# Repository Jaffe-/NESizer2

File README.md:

## NESizer2: 2A03 Synthesizer Project

The main idea of this project is to use an isolated NES 2A03 CPU/APU IC as a stand-alone synthesizer, controlled by an Atmel Atmega microcontroller. (The project is named NESizer2 after a failed attempt to create a NES synthesizer using only the 2A03 alone, with its own ROM, RAM and I/O logic.)

The 2A03 IC consists of a 6502 CPU core (with some minor changes), a DMA controller and the Audio Processing Unit. The APU is controlled via 22 registers, which are connected internally to the 6502 only; there are no external input pins facilitating communication with the APU directly. This means that in order to control the APU, the 6502 must act as a proxy: The microcontroller must send the 6502 instructions to take a value and put it in a desired APU register.

This project is inspired by a similar approach taken here: http://www.soniktech.com/tsundere/, but the idea here is to have the microcontroller communicate more directly with the 2A03, with a minimum of circuitry to do so.

Check out the most recent demo [here](https://www.youtube.com/watch?v=pXKrs0bFvvk)!

See the documentation for a description of how the NESizer works:

- [Hardware documentation](docs/hardware.md)
- [Software documentation](docs/software.md)

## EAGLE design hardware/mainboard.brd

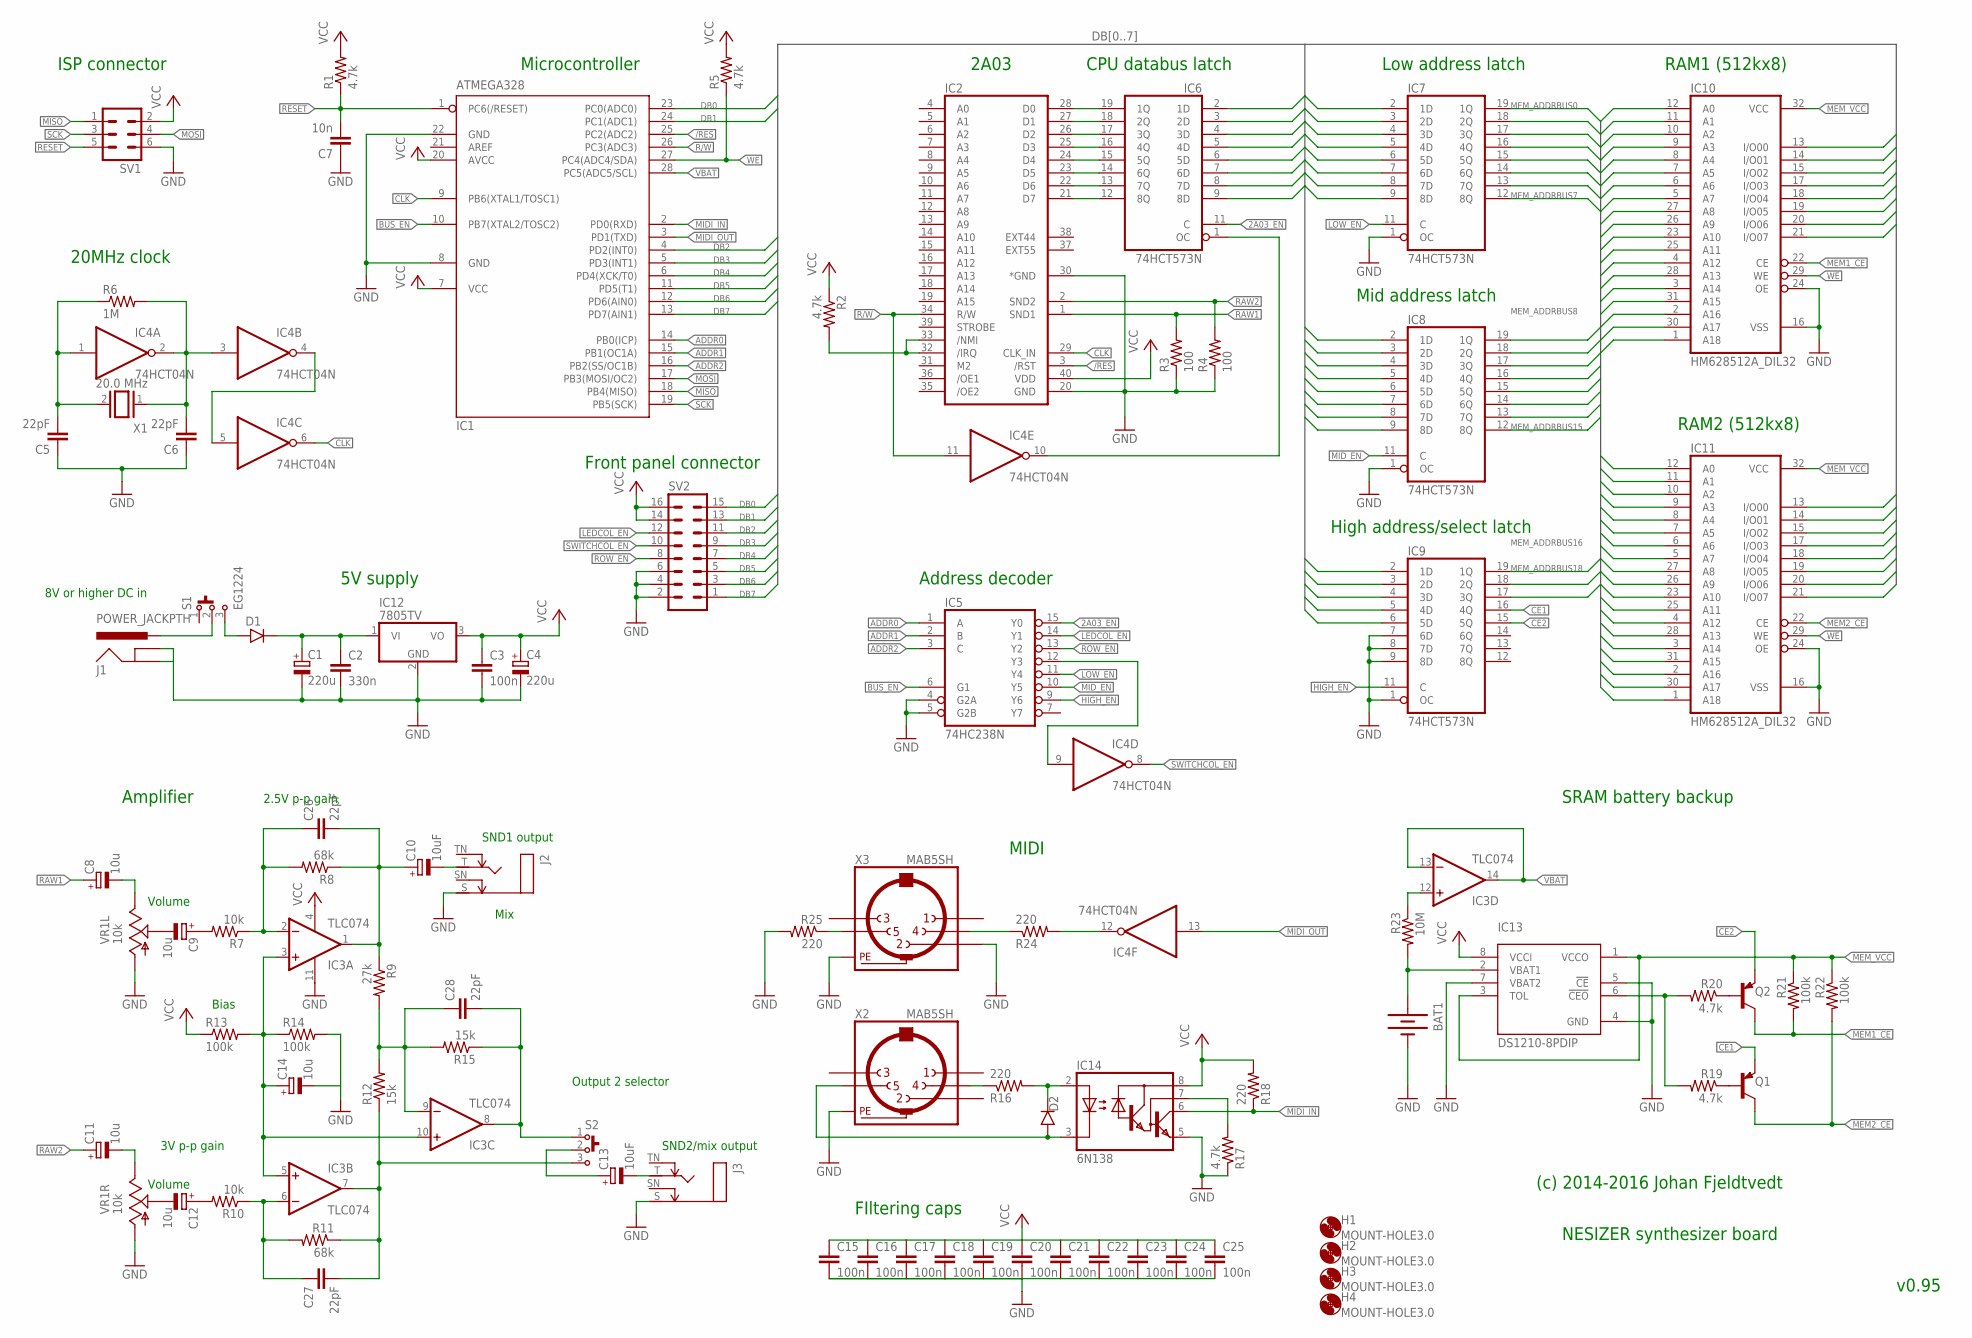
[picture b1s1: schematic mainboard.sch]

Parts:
BAT1: BATTERY20PTH; BATTCOM_20MM_PTH
C1, C4: 220u; E5-10,5
C2: 330n; C025-025X050
C3, C15, C16, C17, C18, C19, C20, C21, C22, C23, C24, C25: 100n; C025-025X050
C5, C6, C26, C27, C28: 22pF; C2.5-2
C7: 10n; C2.5-2
C8, C9, C11, C12, C14: 10u; E2-5
C10, C13: 10uF; E2-5
D1: 1N400X.3; DO41-3
D2: 1N914.3; DO35-3
H1, H2, H3, H4: MOUNT-HOLE3.0; 3,0
IC1: ATMEGA328; DIL28-3
IC2: 2A03; DIL40
IC3: TLC074; DIL14
IC4: 74HCT04N; DIL14
IC5: 74HC238N; DIL16
IC6, IC7, IC8, IC9: 74HCT573N; DIL20
IC10, IC11: HM628512A_DIL32; DIL32
IC12: 7805TV; TO220V
IC13: DS1210-8PDIP; DIL08
IC14: 6N138; DIL08
J1: POWER_JACKPTH; POWER_JACK_PTH
J2, J3: MONOSW; NMJ4HCD2
Q1, Q2: BC557; TO92
R1, R2, R5, R17, R19, R20: 4.7k; 0207/7
R3, R4: 100; 0207/7
R6: 1M; 0207/7
R7, R10: 10k; 0207/7
R8, R11: 68k; 0207/7
R9: 27k; 0207/7
R12, R15: 15k; 0207/7
R13, R14, R21, R22: 100k; 0207/7
R16, R18, R24, R25: 220; 0207/7
R23: 10M; 0207/7
S1, S2: EG1224
SV1: MA03-2
SV2: MA08-2
VR1: 10k; ALPS_RK0971221Z0X
X1: 20.0 MHz; QS
X2, X3: MAB5SH

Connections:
2A03_EN: IC5.15 (Y0), IC6.11 (C)
/RES: IC1.25 (PC2(ADC2)), IC2.3 (/RST)
ADDR0: IC1.14 (PB0(ICP)), IC5.1 (A)
ADDR1: IC1.15 (PB1(OC1A)), IC5.2 (B)
ADDR2: IC1.16 (PB2(SS/OC1B)), IC5.3 (C)
BUS_EN: IC1.10 (PB7(XTAL2/TOSC2)), IC5.6 (G1)
C6: C8.-, VR1.I1 (3)
CE1: IC9.16 (4Q), Q1.1 (E)
CE2: IC9.15 (5Q), Q2.1 (E)
CLK: IC1.9 (PB6(XTAL1/TOSC1)), IC2.29 (CLK_IN), IC4.6 (O)
DB0: IC1.23 (PC0(ADC0)), IC6.2 (1D), IC7.2 (1D), IC8.2 (1D), IC9.2 (1D), IC10.13 (I/O00), IC11.13 (I/O00), SV2.15
DB1: IC1.24 (PC1(ADC1)), IC6.3 (2D), IC7.3 (2D), IC8.3 (2D), IC9.3 (2D), IC10.14 (I/O01), IC11.14 (I/O01), SV2.13
DB2: IC1.4 (PD2(INT0)), IC6.4 (3D), IC7.4 (3D), IC8.4 (3D), IC9.4 (3D), IC10.15 (I/O02), IC11.15 (I/O02), SV2.11
DB3: IC1.5 (PD3(INT1)), IC6.5 (4D), IC7.5 (4D), IC8.5 (4D), IC9.5 (4D), IC10.17 (I/O03), IC11.17 (I/O03), SV2.9
DB4: IC1.6 (PD4(XCK/T0)), IC6.6 (5D), IC7.6 (5D), IC8.6 (5D), IC9.6 (5D), IC10.18 (I/O04), IC11.18 (I/O04), SV2.7
DB5: IC1.11 (PD5(T1)), IC6.7 (6D), IC7.7 (6D), IC8.7 (6D), IC10.19 (I/O05), IC11.19 (I/O05), SV2.5
DB6: IC1.12 (PD6(AIN0)), IC6.8 (7D), IC7.8 (7D), IC8.8 (7D), IC10.20 (I/O06), IC11.20 (I/O06), SV2.3
DB7: IC1.13 (PD7(AIN1)), IC6.9 (8D), IC7.9 (8D), IC8.9 (8D), IC10.21 (I/O07), IC11.21 (I/O07), SV2.1
GND: BAT1.2 (-), C1.-, C2.2, C3.2, C4.-, C5.1, C6.1, C7.1, C14.-, C15.2, C16.2, C17.2, C18.2, C19.2, C20.2, C21.2, C22.2, C23.2, C24.2, C25.2, IC1.8 (GND), IC1.22 (GND), IC2.20 (GND), IC2.30 (*GND), IC3.11 (V-), IC4.7 (GND), IC5.4 (G2A), IC5.5 (G2B), IC5.8 (GND), IC6.10 (GND), IC7.1 (OC), IC7.10 (GND), IC8.1 (OC), IC8.10 (GND), IC9.1 (OC), IC9.7 (6D), IC9.8 (7D), IC9.9 (8D), IC9.10 (GND), IC10.16 (VSS), IC10.24 (OE), IC11.16 (VSS), IC11.24 (OE), IC12.2 (GND), IC13.4 (GND), IC13.5 (!CE), IC13.7 (VBAT2), IC14.5 (GND), J1.GND, J1.GNDBREAK, J2.S, J3.S, R3.1, R4.1, R14.2, R17.1, R25.2, SV1.6, SV2.2, SV2.4, SV2.6, VR1.G1 (1), VR1.G2 (1), X2.PE, X2.PE@ (PE), X3.2, X3.PE, X3.PE@ (PE)
HIGH_EN: IC5.9 (Y6), IC9.11 (C)
LEDCOL_EN: IC5.14 (Y1), SV2.12
LOW_EN: IC5.11 (Y4), IC7.11 (C)
MEM1_CE: IC10.22 (CE), Q2.3 (C), R21.2
MEM2_CE: IC11.22 (CE), Q1.3 (C), R22.2
MEM_ADDRBUS0: IC7.19 (1Q), IC10.12 (A0), IC11.12 (A0)
MEM_ADDRBUS1: IC7.18 (2Q), IC10.11 (A1), IC11.11 (A1)
MEM_ADDRBUS2: IC7.17 (3Q), IC10.10 (A2), IC11.10 (A2)
MEM_ADDRBUS3: IC7.16 (4Q), IC10.9 (A3), IC11.9 (A3)
MEM_ADDRBUS4: IC7.15 (5Q), IC10.8 (A4), IC11.8 (A4)
MEM_ADDRBUS5: IC7.14 (6Q), IC10.7 (A5), IC11.7 (A5)
MEM_ADDRBUS6: IC7.13 (7Q), IC10.6 (A6), IC11.6 (A6)
MEM_ADDRBUS7: IC7.12 (8Q), IC10.5 (A7), IC11.5 (A7)
MEM_ADDRBUS8: IC8.19 (1Q), IC10.27 (A8), IC11.27 (A8)
MEM_ADDRBUS9: IC8.18 (2Q), IC10.26 (A9), IC11.26 (A9)
MEM_ADDRBUS10: IC8.17 (3Q), IC10.23 (A10), IC11.23 (A10)
MEM_ADDRBUS11: IC8.16 (4Q), IC10.25 (A11), IC11.25 (A11)
MEM_ADDRBUS12: IC8.15 (5Q), IC10.4 (A12), IC11.4 (A12)
MEM_ADDRBUS13: IC8.14 (6Q), IC10.28 (A13), IC11.28 (A13)
MEM_ADDRBUS14: IC8.13 (7Q), IC10.3 (A14), IC11.3 (A14)
MEM_ADDRBUS15: IC8.12 (8Q), IC10.31 (A15), IC11.31 (A15)
MEM_ADDRBUS16: IC9.19 (1Q), IC10.2 (A16), IC11.2 (A16)
MEM_ADDRBUS17: IC9.18 (2Q), IC10.30 (A17), IC11.30 (A17)
MEM_ADDRBUS18: IC9.17 (3Q), IC10.1 (A18), IC11.1 (A18)
MEM_VCC: IC10.32 (VCC), IC11.32 (VCC), IC13.1 (VCCO), IC13.3 (TOL), R21.1, R22.1
MIDI_IN: IC1.2 (PD0(RXD)), IC14.6 (VO), R18.1
MIDI_OUT: IC1.3 (PD1(TXD)), IC4.13 (I)
MIDI_PIN_4: R16.1, X2.4
MIDI_PIN_5: D2.A, IC14.3 (C), X2.5
MID_EN: IC5.10 (Y5), IC8.11 (C)
MISO: IC1.18 (PB4(MISO)), SV1.1
MOSI: IC1.17 (PB3(MOSI/OC2)), SV1.4
unnamed: C5.2, IC4.1 (I), R6.1, X1.2
unnamed: C6.2, IC4.2 (O), IC4.3 (I), R6.2, X1.1
unnamed: IC2.21 (D7), IC6.12 (8Q)
unnamed: IC2.22 (D6), IC6.13 (7Q)
unnamed: IC2.23 (D5), IC6.14 (6Q)
unnamed: IC2.24 (D4), IC6.15 (5Q)
unnamed: IC2.25 (D3), IC6.16 (4Q)
unnamed: IC2.26 (D2), IC6.17 (3Q)
unnamed: IC2.27 (D1), IC6.18 (2Q)
unnamed: IC2.28 (D0), IC6.19 (1Q)
unnamed: IC4.4 (O), IC4.5 (I)
unnamed: IC4.9 (I), IC5.12 (Y3)
unnamed: C13.+, S2.2
unnamed: C28.1, IC3.9 (-IN), R9.2, R12.2, R15.2
unnamed: C9.+, R7.2
unnamed: IC2.32 (/IRQ), IC2.33 (/NMI), R2.2
unnamed: C11.-, VR1.I2 (3)
unnamed: C26.1, IC3.2 (-IN), R7.1, R8.2
unnamed: IC3.12 (+IN), R23.1
unnamed: IC14.7 (VB), R17.2
unnamed: C12.+, R10.2
unnamed: C10.-, J2.T
unnamed: C13.-, J3.T
unnamed: C27.1, IC3.6 (-IN), R10.1, R11.2
unnamed: C10.+, C26.2, IC3.1 (OUT), R8.1, R9.1
unnamed: C28.2, IC3.8 (OUT), R15.1, S2.1
unnamed: D1.A, S1.3
unnamed: C14.+, IC3.3 (+IN), IC3.5 (+IN), IC3.10 (+IN), R13.2, R14.1
unnamed: IC4.10 (O), IC6.1 (OC)
unnamed: C9.-, VR1.O1 (2)
unnamed: J1.PWR, S1.2
unnamed: C12.-, VR1.O2 (2)
unnamed: IC13.6 (!CEO), R19.2, R20.2
unnamed: D2.C, IC14.2 (A), R16.2
unnamed: C1.+, C2.1, D1.C, IC12.1 (VI)
unnamed: C27.2, IC3.7 (OUT), R11.1, R12.1, S2.3
unnamed: Q1.2 (B), R19.1
unnamed: Q2.2 (B), R20.1
unnamed: BAT1.1 (+), IC13.2 (VBAT1), R23.2
unnamed: IC4.12 (O), R24.2
unnamed: R24.1, X3.4
unnamed: R25.1, X3.5
R/W: IC1.26 (PC3(ADC3)), IC2.34 (R/W), IC4.11 (I)
RAW1: C8.+, IC2.1 (SND1), R3.2
RAW2: C11.+, IC2.2 (SND2), R4.2
RESET: C7.2, IC1.1 (PC6(/RESET)), R1.1, SV1.5
ROW_EN: IC5.13 (Y2), SV2.8
S1: VR1.S1
S2: VR1.S2
SCK: IC1.19 (PB5(SCK)), SV1.3
SWITCHCOL_EN: IC4.8 (O), SV2.10
VBAT: IC1.28 (PC5(ADC5/SCL)), IC3.13 (-IN), IC3.14 (OUT)
VCC: C3.1, C4.+, C15.1, C16.1, C17.1, C18.1, C19.1, C20.1, C21.1, C22.1, C23.1, C24.1, C25.1, IC1.7 (VCC), IC1.20 (AVCC), IC2.40 (VDD), IC3.4 (V+), IC4.14 (VCC), IC5.16 (VCC), IC6.20 (VCC), IC7.20 (VCC), IC8.20 (VCC), IC9.20 (VCC), IC12.3 (VO), IC13.8 (VCCI), IC14.8 (VCC), R1.2, R2.1, R5.2, R13.1, R18.2, SV1.2, SV2.14, SV2.16
WE: IC1.27 (PC4(ADC4/SDA)), IC10.29 (WE), IC11.29 (WE), R5.1

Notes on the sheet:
Microcontroller
2A03
ISP connector
20MHz clock
Amplifier
Address decoder
CPU databus latch
RAM1 (512kx8)
RAM2 (512kx8)
Low address latch
Mid address latch
High address/select latch
Front panel connector
SRAM battery backup
MIDI
5V supply
FIltering caps
SND2/mix output
SND1 output
8V or higher DC in
Volume
Output 2 selector
2.5V p-p gain
3V p-p gain
Mix
v0.95
(c) 2014-2016 Johan Fjeldtvedt
NESIZER synthesizer board
Bias

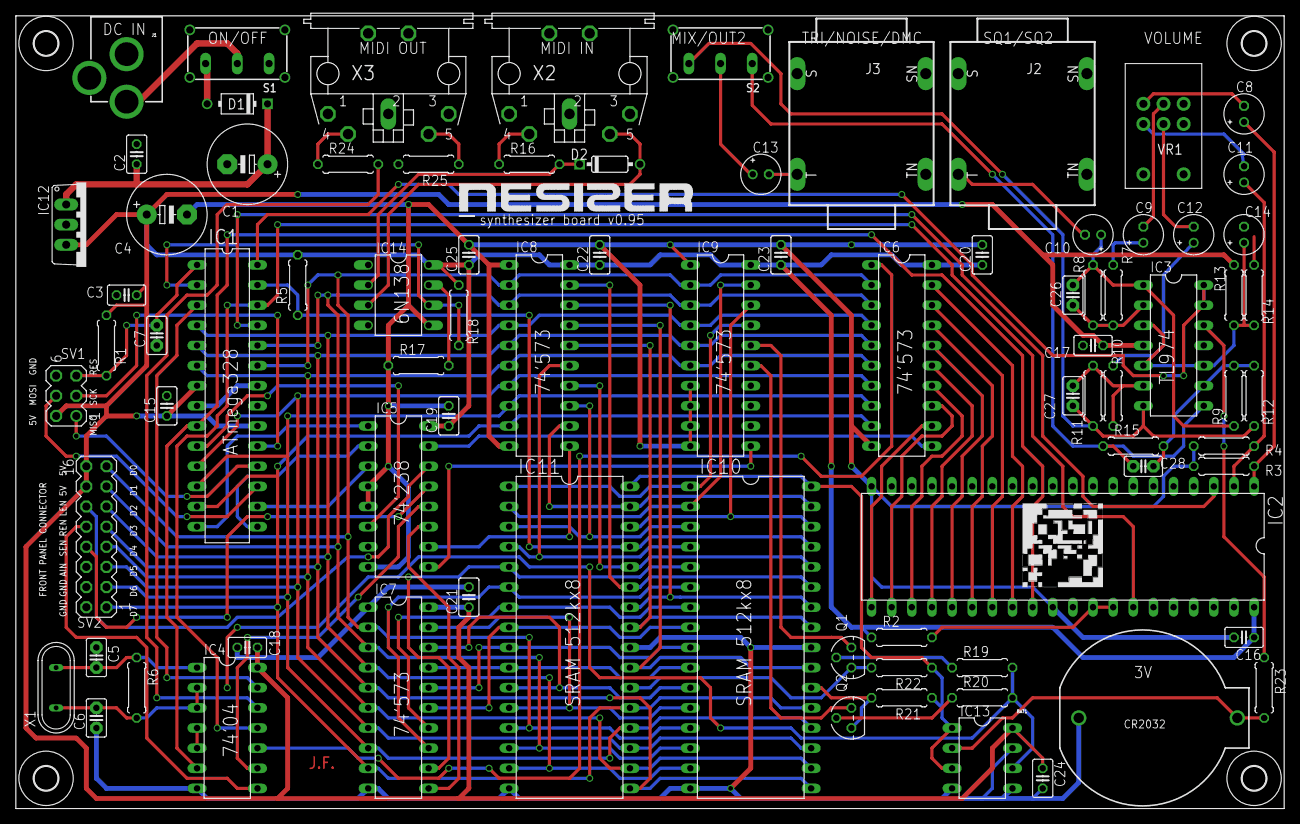
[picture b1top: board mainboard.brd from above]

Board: 2 copper layers, 160.0 x 100.0 mm, 89 parts (0 on the bottom side), 103 nets.

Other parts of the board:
U$1: NESIZER_LOGO
U$2: MARIO

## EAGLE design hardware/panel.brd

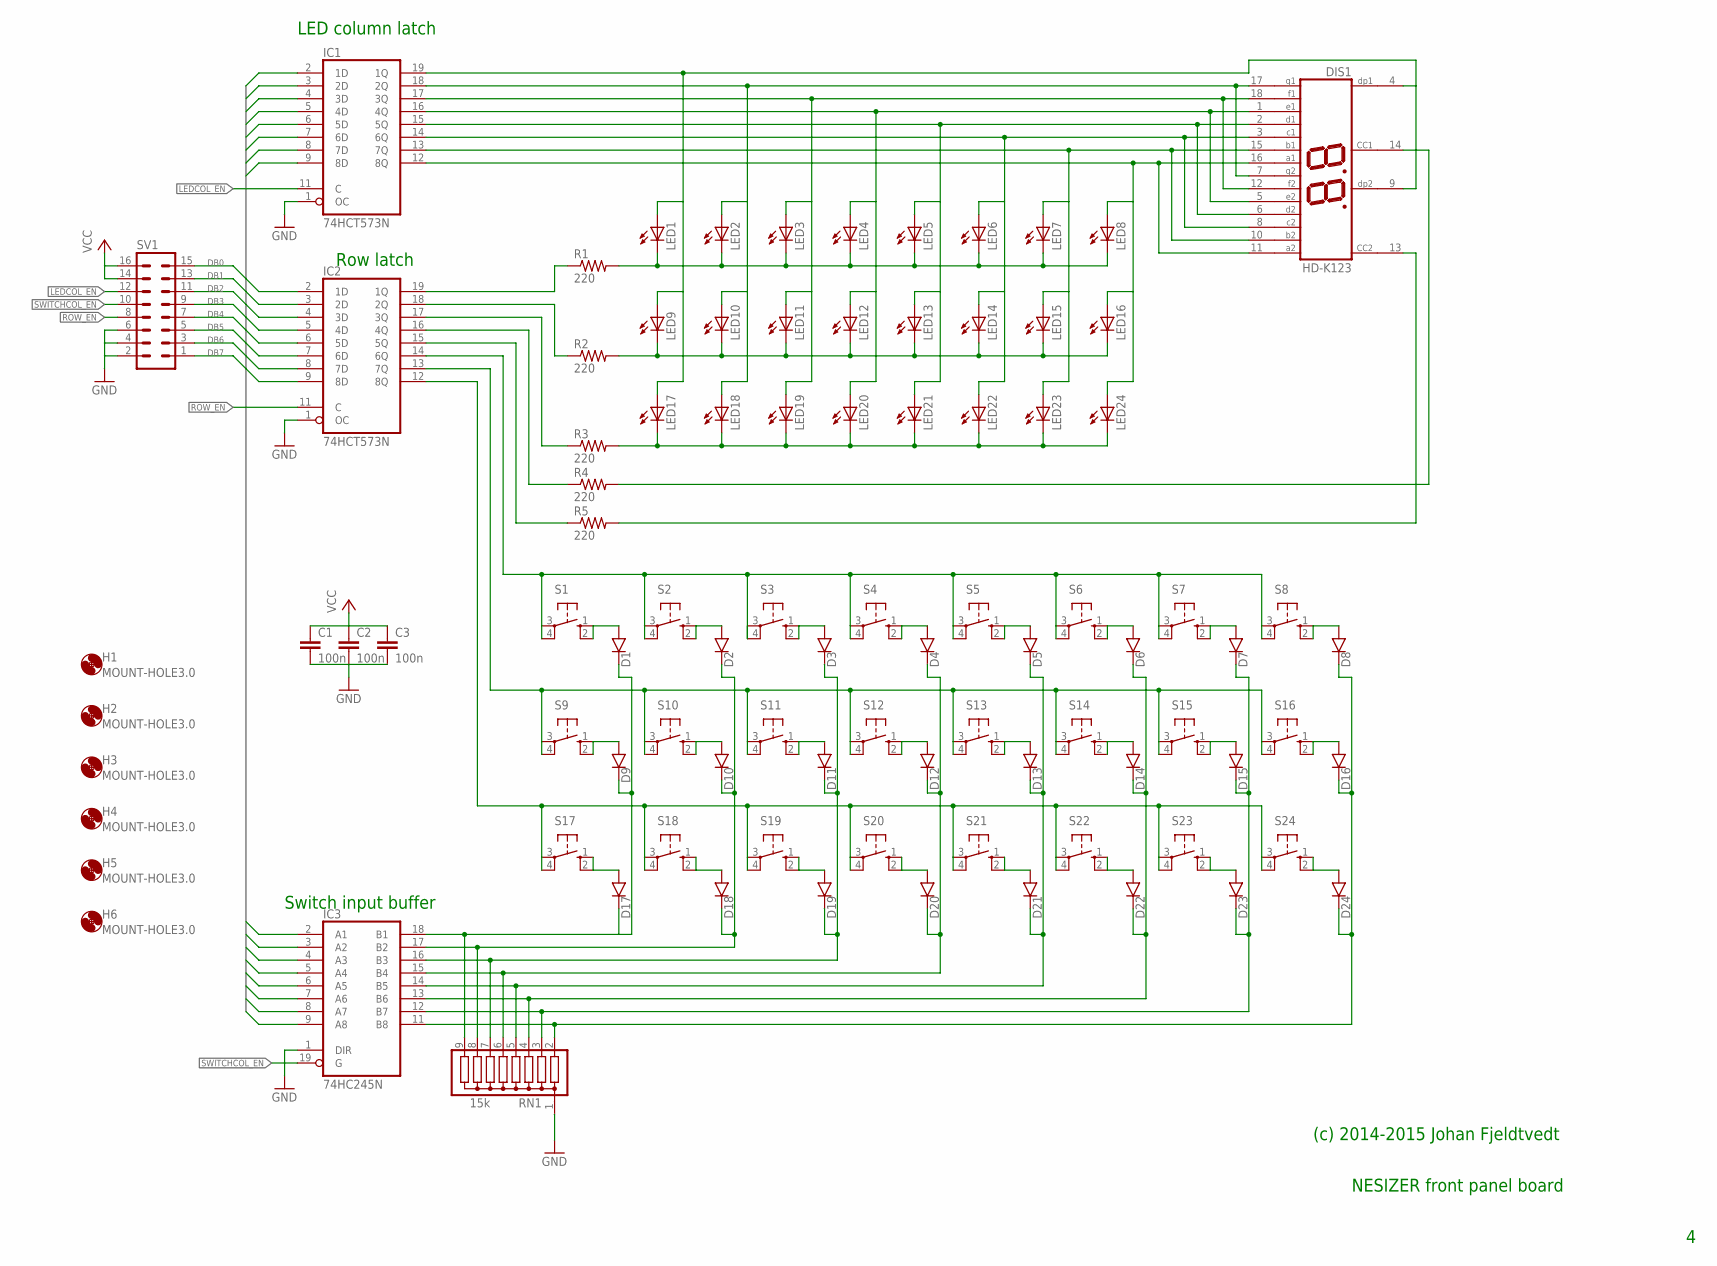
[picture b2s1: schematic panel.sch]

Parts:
C1, C2, C3: 100n; C025-025X050
D1, D2, D3, D4, D5, D6, D7, D8, D9, D10, D11, D12, D13, D14, D15, D16, D17, D18, D19, D20, D21, D22, D23, D24: 1N914.3; DO35-3
DIS1: HD-K123; HDSP-R
H1, H2, H3, H4, H5, H6: MOUNT-HOLE3.0; 3,0
IC1, IC2: 74HCT573N; DIL20
IC3: 74HC245N; DIL20
LED1, LED2, LED3, LED4, LED5, LED6, LED7, LED8, LED9, LED10, LED11, LED12, LED13, LED14, LED15, LED16, LED17, LED18, LED19, LED20, LED21, LED22, LED23, LED24: LED3MM
R1, R2, R3, R4, R5: 220; 0207/7
RN1: 15k; SIL9
S1, S2, S3, S4, S5, S6, S7, S8, S9, S10, S11, S12, S13, S14, S15, S16: 40-XX; B3F-40XX
S17, S18, S19, S20, S21, S22, S23, S24: 10-XX; B3F-10XX
SV1: MA08-2

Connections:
DB0: IC1.2 (1D), IC2.2 (1D), IC3.2 (A1), SV1.15
DB1: IC1.3 (2D), IC2.3 (2D), IC3.3 (A2), SV1.13
DB2: IC1.4 (3D), IC2.4 (3D), IC3.4 (A3), SV1.11
DB3: IC1.5 (4D), IC2.5 (4D), IC3.5 (A4), SV1.9
DB4: IC1.6 (5D), IC2.6 (5D), IC3.6 (A5), SV1.7
DB5: IC1.7 (6D), IC2.7 (6D), IC3.7 (A6), SV1.5
DB6: IC1.8 (7D), IC2.8 (7D), IC3.8 (A7), SV1.3
DB7: IC1.9 (8D), IC2.9 (8D), IC3.9 (A8), SV1.1
GND: C1.2, C2.2, C3.2, IC1.1 (OC), IC1.10 (GND), IC2.1 (OC), IC2.10 (GND), IC3.1 (DIR), IC3.10 (GND), RN1.1, SV1.2, SV1.4, SV1.6
LEDCOL_EN: IC1.11 (C), SV1.12
unnamed: LED1.K (C), LED2.K (C), LED3.K (C), LED4.K (C), LED5.K (C), LED6.K (C), LED7.K (C), LED8.K (C), R1.2
unnamed: LED17.K (C), LED18.K (C), LED19.K (C), LED20.K (C), LED21.K (C), LED22.K (C), LED23.K (C), LED24.K (C), R3.2
unnamed: DIS1.4 (DP1), DIS1.9 (DP2), IC1.19 (1Q), LED1.A, LED9.A, LED17.A
unnamed: DIS1.7 (G2), DIS1.17 (G1), IC1.18 (2Q), LED2.A, LED10.A, LED18.A
unnamed: DIS1.12 (F2), DIS1.18 (F1), IC1.17 (3Q), LED3.A, LED11.A, LED19.A
unnamed: DIS1.1 (E1), DIS1.5 (E2), IC1.16 (4Q), LED4.A, LED12.A, LED20.A
unnamed: DIS1.2 (D1), DIS1.6 (D2), IC1.15 (5Q), LED5.A, LED13.A, LED21.A
unnamed: DIS1.3 (C1), DIS1.8 (C2), IC1.14 (6Q), LED6.A, LED14.A, LED22.A
unnamed: DIS1.10 (B2), DIS1.15 (B1), IC1.13 (7Q), LED7.A, LED15.A, LED23.A
unnamed: DIS1.11 (A2), DIS1.16 (A1), IC1.12 (8Q), LED8.A, LED16.A, LED24.A
unnamed: LED9.K (C), LED10.K (C), LED11.K (C), LED12.K (C), LED13.K (C), LED14.K (C), LED15.K (C), LED16.K (C), R2.2
unnamed: IC2.19 (1Q), R1.1
unnamed: DIS1.13 (CC2), R5.2
unnamed: DIS1.14 (CC1), R4.2
unnamed: IC2.17 (3Q), R3.1
unnamed: IC2.15 (5Q), R5.1
unnamed: IC2.16 (4Q), R4.1
unnamed: IC2.13 (7Q), S9.3, S9.4 (P1), S10.3, S10.4 (P1), S11.3, S11.4 (P1), S12.3, S12.4 (P1), S13.3, S13.4 (P1), S14.3, S14.4 (P1), S15.3, S15.4 (P1), S16.3, S16.4 (P1)
unnamed: IC2.18 (2Q), R2.1
unnamed: IC2.14 (6Q), S1.3, S1.4 (P1), S2.3, S2.4 (P1), S3.3, S3.4 (P1), S4.3, S4.4 (P1), S5.3, S5.4 (P1), S6.3, S6.4 (P1), S7.3, S7.4 (P1), S8.3, S8.4 (P1)
unnamed: D2.C, D10.C, D18.C, IC3.17 (B2), RN1.8
unnamed: D1.C, D9.C, D17.C, IC3.18 (B1), RN1.9
unnamed: D9.A, S9.1 (S), S9.2 (S1)
unnamed: D2.A, S2.1 (S), S2.2 (S1)
unnamed: IC2.12 (8Q), S17.3, S17.4 (P1), S18.3, S18.4 (P1), S19.3, S19.4 (P1), S20.3, S20.4 (P1), S21.3, S21.4 (P1), S22.3, S22.4 (P1), S23.3, S23.4 (P1), S24.3, S24.4 (P1)
unnamed: D17.A, S17.1 (S), S17.2 (S1)
unnamed: D18.A, S18.1 (S), S18.2 (S1)
unnamed: D19.A, S19.1 (S), S19.2 (S1)
unnamed: D20.A, S20.1 (S), S20.2 (S1)
unnamed: D21.A, S21.1 (S), S21.2 (S1)
unnamed: D11.A, S11.1 (S), S11.2 (S1)
unnamed: D10.A, S10.1 (S), S10.2 (S1)
unnamed: D4.A, S4.1 (S), S4.2 (S1)
unnamed: D12.A, S12.1 (S), S12.2 (S1)
unnamed: D3.A, S3.1 (S), S3.2 (S1)
unnamed: D3.C, D11.C, D19.C, IC3.16 (B3), RN1.7
unnamed: D5.A, S5.1 (S), S5.2 (S1)
unnamed: D13.A, S13.1 (S), S13.2 (S1)
unnamed: D6.A, S6.1 (S), S6.2 (S1)
unnamed: D14.A, S14.1 (S), S14.2 (S1)
unnamed: D22.A, S22.1 (S), S22.2 (S1)
unnamed: D7.A, S7.1 (S), S7.2 (S1)
unnamed: D15.A, S15.1 (S), S15.2 (S1)
unnamed: D23.A, S23.1 (S), S23.2 (S1)
unnamed: D8.A, S8.1 (S), S8.2 (S1)
unnamed: D16.A, S16.1 (S), S16.2 (S1)
unnamed: D24.A, S24.1 (S), S24.2 (S1)
unnamed: D4.C, D12.C, D20.C, IC3.15 (B4), RN1.6
unnamed: D5.C, D13.C, D21.C, IC3.14 (B5), RN1.5
unnamed: D6.C, D14.C, D22.C, IC3.13 (B6), RN1.4
unnamed: D7.C, D15.C, D23.C, IC3.12 (B7), RN1.3
unnamed: D8.C, D16.C, D24.C, IC3.11 (B8), RN1.2
unnamed: D1.A, S1.1 (S), S1.2 (S1)
ROW_EN: IC2.11 (C), SV1.8
SWITCHCOL_EN: IC3.19 (G), SV1.10
VCC: C1.1, C2.1, C3.1, IC1.20 (VCC), IC2.20 (VCC), IC3.20 (VCC), SV1.14, SV1.16

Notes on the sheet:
LED column latch
Row latch
Switch input buffer
NESIZER front panel board
(c) 2014-2015 Johan Fjeldtvedt

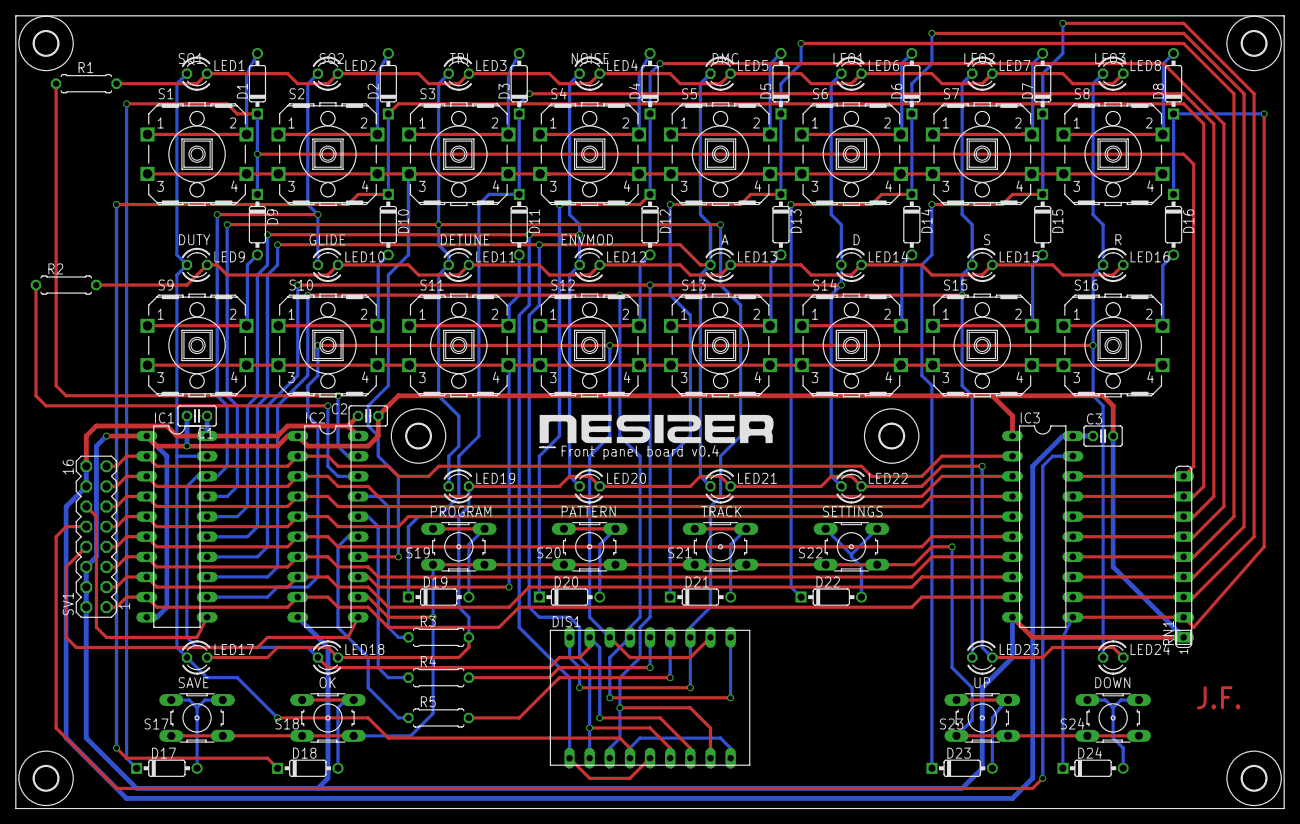
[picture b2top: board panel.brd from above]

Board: 2 copper layers, 160.0 x 100.0 mm, 93 parts (0 on the bottom side), 66 nets.

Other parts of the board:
U$1: NESIZER_LOGO

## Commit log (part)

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2014-08-03 7 segment added
2014-08-04 sine table put in flash
2014-08-04 README update
2014-08-08 schematic updates
2014-08-09 fixes and new register write routine
2014-08-14 SRAM support added
2014-08-19 new schematics in README.md
2014-08-20 bufixes and added patchmemory
2014-08-20 changed README
2014-08-22 new readme
2014-08-25 UI fixes. New readme
2014-08-29 new schematic with SRAM battery circuit fix
2014-08-31 new schematic with MIDI input
2014-09-22 mainboard updates
2014-10-22 memory is now quicker to access serially
2014-11-03 panel board updates
2014-11-12 readme
2014-11-19 fixed component names
2015-01-24 restructuring
2015-01-29 changed buttons on panel board
2015-02-13 restructure
2015-02-26 new LFO scheme
2015-02-26 timing.c/h merged into task.c/h
2015-03-01 fixed sample transfer bug, added progress bar
2015-03-02 cleanup
2015-03-05 bugfixes
2015-03-07 moved assembly code to own file
2015-03-08 fixed apu
2015-03-09 cleaned up cent -> period code
2015-04-11 changed audio amp
2015-05-04 compressed button led states
2015-07-14 input.c: cleanup
2015-07-14 add bus_deselect when setting leds
2015-07-14 add field names to struct array declaration for clarity
2015-08-08 add GPLv3 to 2a03_io.c
2015-08-08 Bring github ajour
    git has so far been used solely as a way to dump stuff to github.
    It will now be used more actively in the development process. This
    commit is the last 'dump' commit. It adds local work that has been
    done over the last months:
    - Add GPLv3 to all files
    - Stylistic change: do not use typedefs for structs and enums
2015-08-09 Make internal functions static
2015-08-09 remove old APU library description
2015-08-11 add data/sine.c to git
2015-08-11 remove ui_track.h include
2015-08-13 rename 2a03_asm.s to 2a03_io.s
2015-08-14 restructure: group source files into submodule directories
    Mostly for easier navigation, but also for easier stubbing and mocking
    to do better testing on the host platform instead of on the hardware.
2015-08-15 make register_write inline
2015-08-16 Added Gitter badge
2015-08-20 Remove TARGET ifdef
    Instead of building a stubbed x86-version, simavr will be used for
    prototyping on PC instead. No need to clutter the codebase with ugly
    ifdefs.
2015-08-23 Add headers to makefile dependencies
2015-10-28 mainboard: new schematic snapshot
2015-11-13 New battery backup circuit
    The DS1210 is expensive and found to not really be needed here, so it has been
    replaced by a discrete transistor circuit.
    The op-amp used for the bias voltage buffer in the audio amplifier is now used
    for buffering the battery voltage instead. Its output is now connected to ADC5
    of the ATmega to allow for reading the battery voltage.
2015-11-14 Split README.md into not-so-huge sections
2015-11-20 Update hardware.md: removed DS1210 references
2015-12-18 added sch and brd files for hardware
2015-12-21 add script for generating period tables
2015-12-21 put period tables in included file
2015-12-21 use float instead of integer division
2016-01-01 add link to periods.pdf in software.md
2016-01-08 2a03.c: sweep fix implemented for both square channels
2016-01-08 2a03.c: clean up the sweep fix code (still ugly though ..)
2016-01-10 remove ENVMOD parameters
2016-01-10 remove SHIFT button as it makes the UI too complex to use
2016-01-10 remove shift-enabled parameters
2016-01-10 change pitchbend maximum to two octaves
2016-01-10 remove shift button code in ui_programmer
2016-01-19 LED states now occupy 6 and not 24 bytes; reduce array sizes correpsondingly
2016-01-19 fix LED defines
2016-01-19 add assigner UI module
2016-01-19 sequencer_leds needs only be 6 bytes
2016-01-19 replace mode switch with table
2016-01-20 save previous mode when doing getvalue in ui_programmer
2016-01-21 start adding assigner
2016-01-24 expand coarse range
2016-01-25 rename getvalue states
2016-01-25 fix bug where UP lights up when in getvalue mode
2016-01-25 use enum for assigner modes
2016-01-25 warning fix: add pointer cast to ARP_MODE parameter
2016-01-27 remove old notes array
2016-01-27 started refactoring MIDI code to support polyphony
2016-01-27 remove old assigner code
2016-01-27 rename NOTE_LIST_MAX to MIDI_NOTE_LIST_MAX
2016-01-27 rename midi_channel_put to midi_channel_apply
2016-01-28 ui_programmer: make state static
2016-01-28 set assign_midi_chn before starting a getvalue session to load previous value
2016-01-31 fix assigner_mode enum values: default is MONO and has value 0
2016-01-31 flesh out assigner_handler. now handles MONO assignment for one voice
2016-01-31 store LFOs in array instead of separate variables
2016-01-31 clean up assigner code (still very rudimentary)
2016-03-07 Makefile: add dependecies on headers
2016-03-07 use int8_t for group ids
2016-05-31 add manual.tex
2016-06-15 fix ARP SYNC compiler error
2016-11-07 HW 0.9 fix
    Added missing trace from battery to op-amp
2016-11-12 Clean up manual
    The manual was kept poorly out of sync with the actual user interface
    code, so a lot of the button positions were wrong.
    The sequencer description has also been removed until it is actually
    implemented.
2016-11-12 replace coarse tuning with octave setting
2016-11-13 add battery checking on bootup and in UI
    It is now possible to press S7 when in the settings mode to check the
    voltage on the battery (board revision >= 0.8)
    On startup, the voltage will be compared to 2.5V, and a warning ('bL'
    flashing on the display) will be given if it is.
2016-11-14 update manual with new assignment modes
2016-11-14 make it possible to select split point directly on keyboard
    When in getvalue mode and the parameter type is NOTE, incoming MIDI
    notes will be forwarded to getvalue and used as the parameter value,
    immediately exiting getvalue mode.
2016-11-14 main.c: add include of battery.h
2016-11-16 fix MIDI sample uploading
    The MIDI sample transfer code was not changed to work with the newest UI
    framework. A null function pointer caused the system to restart when a
    sample is transferred via MIDI.
2016-11-16 add tempo control to sequencer
    up/down when playing will alter the tempo
2016-11-16 clean up LFOs
    Just use signed integers in LFO code to make it simpler.
    The LFOs are now updated every tick instead of every 10*tick.
    This makes the resolution on the frequency setting a lot smoother (but
    some scaling is needed in the UI to map 0-99 to the best possible range)
2016-11-18 add MIDI clocking of sequencer
    The sequencer can now be clocked via MIDI. A scale setting is added to
    be able to select the 'resolution' of the sequence. It selects whether
    the 16 step sequence is 1, 2 or 4 bars (i.e. if each step represents a
    16th, 8th or quarter note)
2016-11-18 Bump period and priority of sequencer task
    The sequencer task should run a bit faster to allow better resolution
    for the tempo timer.
2017-01-29 fix bug in noise envelope modulation
2017-01-29 add functionality for formatting pattern storage
    Adds a function for initializing the pattern memory to empty
    patterns.
2017-02-08 mainboard v0.95: fixes and MIDI out
    Fixed faults with battery measurement and RESET circuitry.
    Added MIDI OUT connector.
2017-02-08 clean up io/bus
2017-02-09 move BUS_EN from PD1 to PB7
    Since PD1 is going to be used for MIDI TX.
2017-02-09 make ring buffer into its own data structure
    MIDI out requires an additional ring buffer, so split this out into its
    own data structure and create two instances of it for input and output.
2017-02-09 remove redundant zeros from message length array
2017-02-09 update manual with MIDI out information
2017-02-11 clean up warnings
2017-03-05 add sequence clean function
2017-03-05 apu: remove redundant functions
2023-06-23 handle NoteOn,Vel=0 same as NoteOff
    per MIDI Spec compliance, a NoteOn command with Velocity = 0 should be treated identically to NoteOff
2023-06-23 Handle NoteOn,Vel=0 same as NoteOff (#12)
    * handle NoteOn,Vel=0 same as NoteOff
    per MIDI Spec compliance, a NoteOn command with Velocity = 0 should be treated identically to NoteOff
    * Handle NoteOn,Vel=0 same as NoteOff
    Updated MIDI input code to comply with MIDI specification regarding stopping playback of notes.
    A NoteOn command with Velocity = 0 should be treated identically to NoteOff.
2023-08-27 improve initial startup behavior
    Add a simple check for whether the RAM contains valid data or not.
    If the expected magic data is not found, re-initialize the memory
    before continuing the boot process. Also log the error for display
    later.
2023-09-09 main: place magic section at address 4
    Having the magic words start at address 0 seems to not work correctly,
    either because of a hardware issue or some rogue part of the firmware
    which writes to address 0.
    Move the words to start at address 4, this seems to not cause issues.
2023-09-10 rework initial channel silencing
    Remove the 'misc' task and instead silence the channels in a simpler
    way.
2023-09-10 add simple memory dump to settings
    Button 12 in settings, up/down can be used to scroll through memory
    bytes.
2023-09-13 minor change in 2a03 setup sequence
    Set port value register before direction register.
2023-10-02 apu: return early from update handler if not enabled
2023-10-02 sample: use new tree based allocator
    Don't do a linear block search each time a block needs to be allocated.
    Instead use free bits in each block entry to implement a tree such that
    block allocations can be done in just 5 steps.
2023-10-02 ui: settings: add some convenience buttons in memory debugger
2023-10-09 midi: remove midi rx from midi_io_handler
    This is now handled by the dedicated interrupt for UART RX
2023-10-09 Makefile: -O2 and default to atmega328p MCU type
    Default to atmega328p as that is what is used in the BOM and probably
    used by most users.
    Use O2 optimization level. O3 has been used so far, but now flash space
    is getting tight. The critical part is guaranteeing that DMC sample
    playback gets to tick at approximately 16 kHz, which still seems doable
    with -O2.
2023-11-17 Added midi CC support
2023-11-17 Updates to the Midi cc range logic
2023-11-19 Match code style and move const to PROGMEM
2024-04-05 fix all errors caught, to compile using VSCode
2024-04-07 included comm ports for both windows and linux
2024-04-09 include library and header for serial debugging
2024-04-09 Support booting without 2A03 installed
    Support booting the NESizer without a 2A03 chip installed.
    To check for 2A03 presence, the interrupt on the PC3 (R/W) pin is
    enabled and used to count toggles on the line. Testing shows that on
    average a regular 2A03 (divisor 12) will cause the count to become ~110
    during a 10 us window. This value will be lower for chips with higher
    clock divisors, so the threshold is set to a count of 10 to keep a good
2024-04-15 PlatformIO: use -O2 build optimization
    Add missing build setting for optimization level. Set to -O2 as in
    Makefile.
2024-05-05 serial debug test
2024-05-05 fixed tiny typo
2024-05-06 added handler for debug text strings and more byte message types
2024-05-06 included code for ESP32 serial debug monitor in tools/
2024-06-21 fixed "parameter name omitted" compile error
2024-09-16 use previous retrigger behavior for DMC channel
2024-09-16 ignore irrelevant sysex messages (to avoid hang)
2024-09-20 added patch selection via midi program change, and separated note_code
2024-09-20 sysex handling rework
2024-09-21 troubleshooting sysex handling
2024-09-22 macos port included in Platform IO conf
2024-09-24 add sysex debug mode and hex print
2024-09-24 sysex overhaul, working now
2024-09-24 sysex working perfectly now
2024-10-04 big PR with all the new features (note stacking, CC param adjust, updated SysEx parsing, ProgramChange patch select, and small UI improvements) (#27)
    * Adding gitignore
    * Added midi CC support
    Updated gitignore
    Updates to the Midi cc range logic
    Update: Changed midi CC indexes
    Fixed: added MIDI_CMD_CONTROL_CHANGE to midi_channel_apply

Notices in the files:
parts and their libraries:
SparkFun-Electromechanical: Licensing: CC v3.0 Share-Alike You are welcome to use this library for commercial purposes.
switch-e-switch: Copyright (C) 2010, Bob Starr
